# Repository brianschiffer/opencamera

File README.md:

# opencamera
an open hardware CCD camera

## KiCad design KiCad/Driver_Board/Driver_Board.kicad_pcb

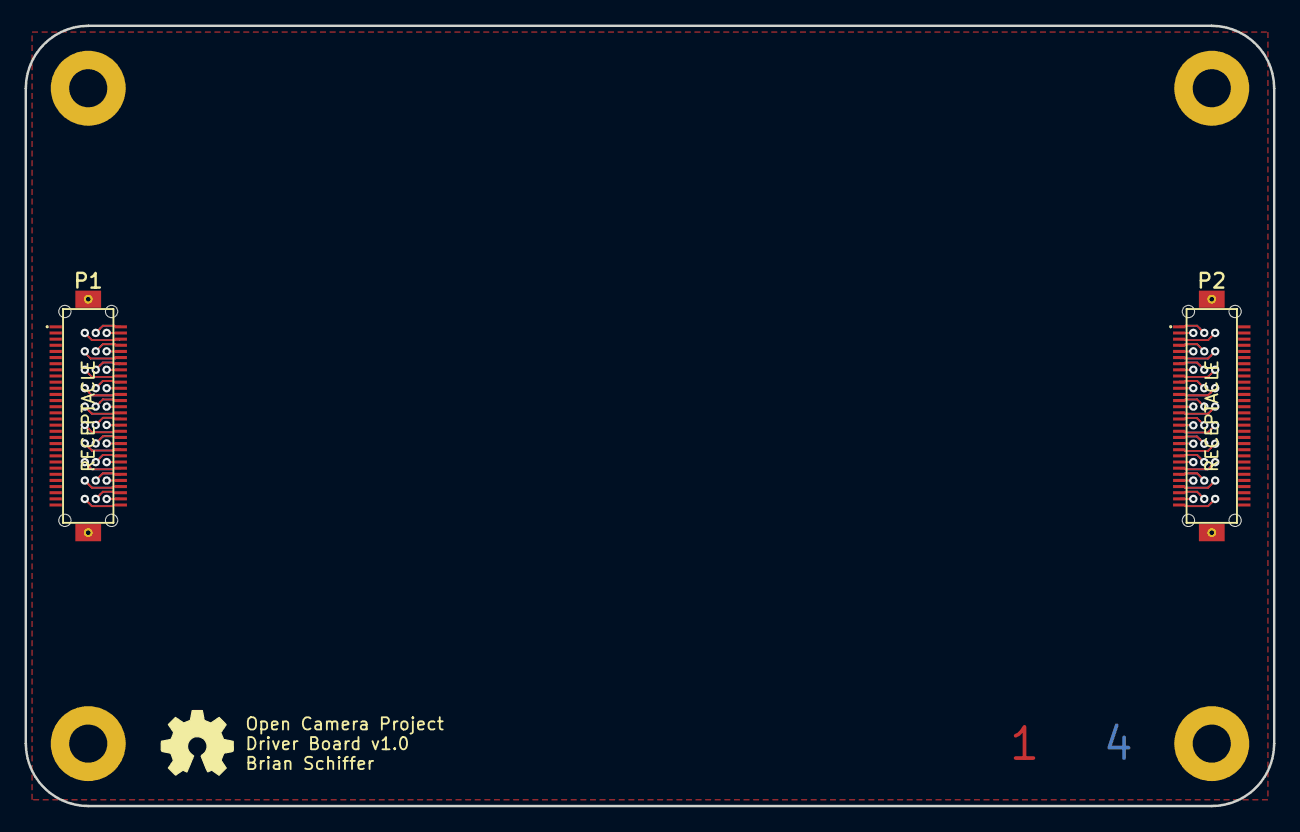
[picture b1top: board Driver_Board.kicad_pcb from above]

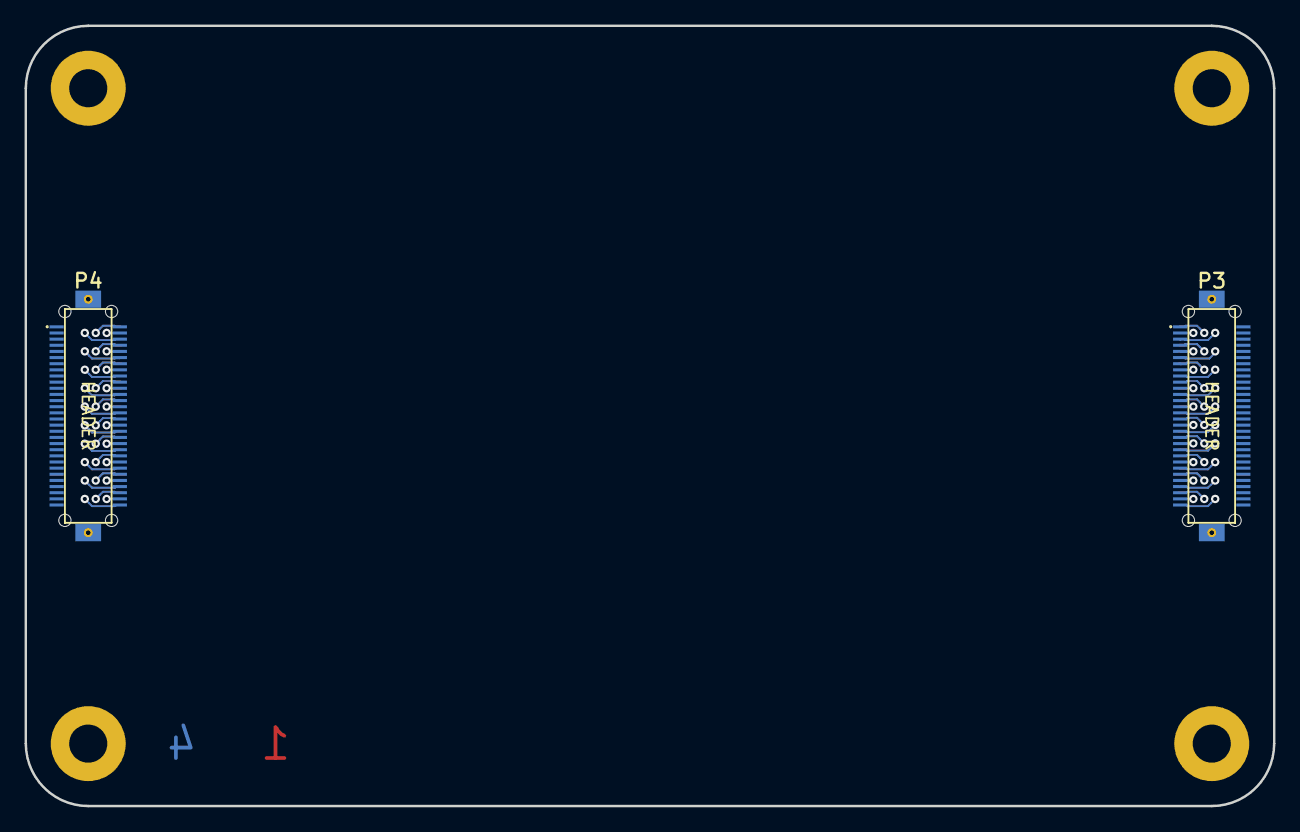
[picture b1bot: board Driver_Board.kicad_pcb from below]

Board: 4 copper layers, 101.6 x 63.5 mm, 4 parts (2 on the bottom side), 62 nets.

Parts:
P1: CONN_LEFT_TOP; DF17_60_RECEPTACLE
P2: CONN_RIGHT_TOP; DF17_60_RECEPTACLE
P3: CONN_LEFT_BOTTOM; DF17_60_HEADER
P4: CONN_RIGHT_BOTTOM; DF17_60_HEADER

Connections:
/connectors/L1: P1.2, P3.1
/connectors/L2: P1.4, P3.3
/connectors/L3: P1.6, P3.5
/connectors/L4: P1.8, P3.7
/connectors/L5: P1.10, P3.9
/connectors/L6: P1.12, P3.11
/connectors/L7: P1.14, P3.13
/connectors/L8: P1.16, P3.15
/connectors/L9: P1.18, P3.17
/connectors/L10: P1.20, P3.19
/connectors/L11: P1.22, P3.21
/connectors/L12: P1.24, P3.23
/connectors/L13: P1.26, P3.25
/connectors/L14: P1.28, P3.27
/connectors/L15: P1.30, P3.29
/connectors/L16: P1.32, P3.31
/connectors/L17: P1.34, P3.33
/connectors/L18: P1.36, P3.35
/connectors/L19: P1.38, P3.37
/connectors/L20: P1.40, P3.39
/connectors/L21: P1.42, P3.41
/connectors/L22: P1.44, P3.43
/connectors/L23: P1.46, P3.45
/connectors/L24: P1.48, P3.47
/connectors/L25: P1.50, P3.49
/connectors/L26: P1.52, P3.51
/connectors/L27: P1.54, P3.53
/connectors/L28: P1.56, P3.55
/connectors/L29: P1.58, P3.57
/connectors/L30: P1.60, P3.59
/connectors/R1: P2.1, P4.2
/connectors/R2: P2.3, P4.4
/connectors/R3: P2.5, P4.6
/connectors/R4: P2.7, P4.8
/connectors/R5: P2.9, P4.10
/connectors/R6: P2.11, P4.12
/connectors/R7: P2.13, P4.14
/connectors/R8: P2.15, P4.16
/connectors/R9: P2.17, P4.18
/connectors/R10: P2.19, P4.20
/connectors/R11: P2.21, P4.22
/connectors/R12: P2.23, P4.24
/connectors/R13: P2.25, P4.26
/connectors/R14: P2.27, P4.28
/connectors/R15: P2.29, P4.30
/connectors/R16: P2.31, P4.32
/connectors/R17: P2.33, P4.34
/connectors/R18: P2.35, P4.36
/connectors/R19: P2.37, P4.38
/connectors/R20: P2.39, P4.40
/connectors/R21: P2.41, P4.42
/connectors/R22: P2.43, P4.44
/connectors/R23: P2.45, P4.46
/connectors/R24: P2.47, P4.48
/connectors/R25: P2.49, P4.50
/connectors/R26: P2.51, P4.52
/connectors/R27: P2.53, P4.54
/connectors/R28: P2.55, P4.56
/connectors/R29: P2.57, P4.58
/connectors/R30: P2.59, P4.60
GNDA: P2.2, P2.4, P2.6, P2.8, P2.10, P2.12, P2.14, P2.16, P2.18, P2.20, P2.22, P2.24, P2.26, P2.28, P2.30, P2.32, P2.34, P2.36, P2.38, P2.40, P2.42, P2.44, P2.46, P2.48, P2.50, P2.52, P2.54, P2.56, P2.58, P2.60, P2.61, P2.62, P4.1, P4.3, P4.5, P4.7, P4.9, P4.11, P4.13, P4.15, P4.17, P4.19, P4.21, P4.23, P4.25, P4.27, P4.29, P4.31, P4.33, P4.35, P4.37, P4.39, P4.41, P4.43, P4.45, P4.47, P4.49, P4.51, P4.53, P4.55, P4.57, P4.59, P4.61, P4.62
GNDD: P1.1, P1.3, P1.5, P1.7, P1.9, P1.11, P1.13, P1.15, P1.17, P1.19, P1.21, P1.23, P1.25, P1.27, P1.29, P1.31, P1.33, P1.35, P1.37, P1.39, P1.41, P1.43, P1.45, P1.47, P1.49, P1.51, P1.53, P1.55, P1.57, P1.59, P1.61, P1.62, P3.2, P3.4, P3.6, P3.8, P3.10, P3.12, P3.14, P3.16, P3.18, P3.20, P3.22, P3.24, P3.26, P3.28, P3.30, P3.32, P3.34, P3.36, P3.38, P3.40, P3.42, P3.44, P3.46, P3.48, P3.50, P3.52, P3.54, P3.56, P3.58, P3.60, P3.61, P3.62

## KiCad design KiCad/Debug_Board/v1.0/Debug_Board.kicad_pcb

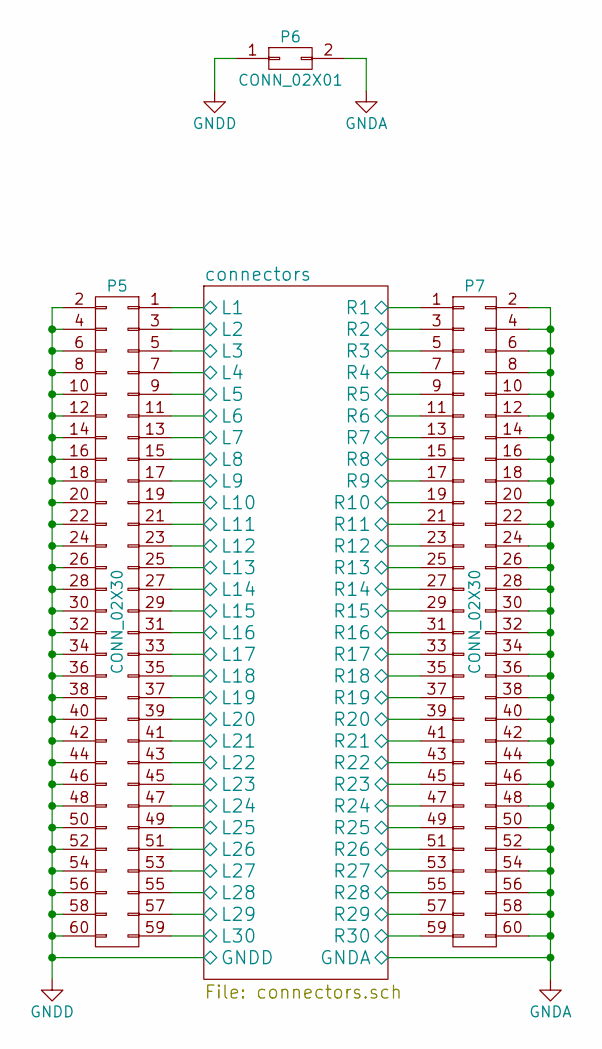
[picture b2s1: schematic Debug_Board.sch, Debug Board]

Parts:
P5, P7: CONN_02X30
P6: CONN_02X01

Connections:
/connectors/L1: P5.1; also elsewhere on the board
/connectors/L2: P5.3; also elsewhere on the board
/connectors/L3: P5.5; also elsewhere on the board
/connectors/L4: P5.7; also elsewhere on the board
/connectors/L5: P5.9; also elsewhere on the board
/connectors/L6: P5.11; also elsewhere on the board
/connectors/L7: P5.13; also elsewhere on the board
/connectors/L8: P5.15; also elsewhere on the board
/connectors/L9: P5.17; also elsewhere on the board
/connectors/L10: P5.19; also elsewhere on the board
/connectors/L11: P5.21; also elsewhere on the board
/connectors/L12: P5.23; also elsewhere on the board
/connectors/L13: P5.25; also elsewhere on the board
/connectors/L14: P5.27; also elsewhere on the board
/connectors/L15: P5.29; also elsewhere on the board
/connectors/L16: P5.31; also elsewhere on the board
/connectors/L17: P5.33; also elsewhere on the board
/connectors/L18: P5.35; also elsewhere on the board
/connectors/L19: P5.37; also elsewhere on the board
/connectors/L20: P5.39; also elsewhere on the board
/connectors/L21: P5.41; also elsewhere on the board
/connectors/L22: P5.43; also elsewhere on the board
/connectors/L23: P5.45; also elsewhere on the board
/connectors/L24: P5.47; also elsewhere on the board
/connectors/L25: P5.49; also elsewhere on the board
/connectors/L26: P5.51; also elsewhere on the board
/connectors/L27: P5.53; also elsewhere on the board
/connectors/L28: P5.55; also elsewhere on the board
/connectors/L29: P5.57; also elsewhere on the board
/connectors/L30: P5.59; also elsewhere on the board
/connectors/R1: P7.1; also elsewhere on the board
/connectors/R2: P7.3; also elsewhere on the board
/connectors/R3: P7.5; also elsewhere on the board
/connectors/R4: P7.7; also elsewhere on the board
/connectors/R5: P7.9; also elsewhere on the board
/connectors/R6: P7.11; also elsewhere on the board
/connectors/R7: P7.13; also elsewhere on the board
/connectors/R8: P7.15; also elsewhere on the board
/connectors/R9: P7.17; also elsewhere on the board
/connectors/R10: P7.19; also elsewhere on the board
/connectors/R11: P7.21; also elsewhere on the board
/connectors/R12: P7.23; also elsewhere on the board
/connectors/R13: P7.25; also elsewhere on the board
/connectors/R14: P7.27; also elsewhere on the board
/connectors/R15: P7.29; also elsewhere on the board
/connectors/R16: P7.31; also elsewhere on the board
/connectors/R17: P7.33; also elsewhere on the board
/connectors/R18: P7.35; also elsewhere on the board
/connectors/R19: P7.37; also elsewhere on the board
/connectors/R20: P7.39; also elsewhere on the board
/connectors/R21: P7.41; also elsewhere on the board
/connectors/R22: P7.43; also elsewhere on the board
/connectors/R23: P7.45; also elsewhere on the board
/connectors/R24: P7.47; also elsewhere on the board
/connectors/R25: P7.49; also elsewhere on the board
/connectors/R26: P7.51; also elsewhere on the board
/connectors/R27: P7.53; also elsewhere on the board
/connectors/R28: P7.55; also elsewhere on the board
/connectors/R29: P7.57; also elsewhere on the board
/connectors/R30: P7.59; also elsewhere on the board
GNDA: P6.2, P7.2, P7.4, P7.6, P7.8, P7.10, P7.12, P7.14, P7.16, P7.18, P7.20, P7.22, P7.24, P7.26, P7.28, P7.30, P7.32, P7.34, P7.36, P7.38, P7.40, P7.42, P7.44, P7.46, P7.48, P7.50, P7.52, P7.54, P7.56, P7.58, P7.60; also elsewhere on the board
GNDD: P5.2, P5.4, P5.6, P5.8, P5.10, P5.12, P5.14, P5.16, P5.18, P5.20, P5.22, P5.24, P5.26, P5.28, P5.30, P5.32, P5.34, P5.36, P5.38, P5.40, P5.42, P5.44, P5.46, P5.48, P5.50, P5.52, P5.54, P5.56, P5.58, P5.60, P6.1; also elsewhere on the board

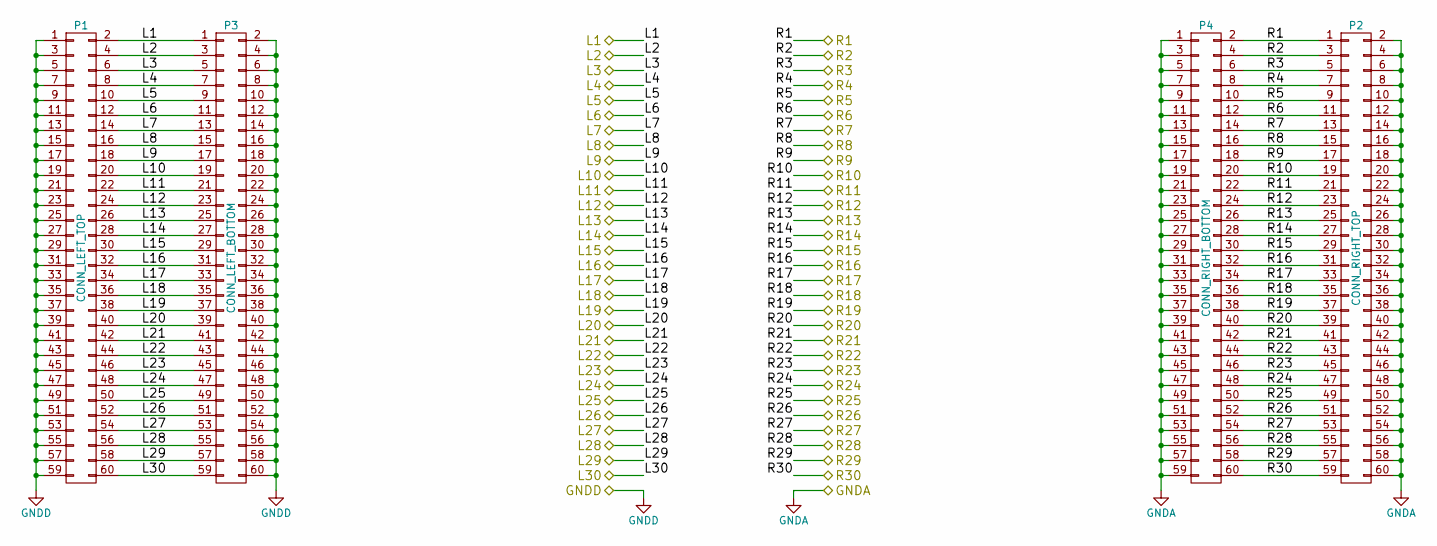
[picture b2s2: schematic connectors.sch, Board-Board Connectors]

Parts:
P1: CONN_LEFT_TOP; DF17_60_RECEPTACLE
P2: CONN_RIGHT_TOP; DF17_60_RECEPTACLE
P3: CONN_LEFT_BOTTOM; DF17_60_HEADER
P4: CONN_RIGHT_BOTTOM; DF17_60_HEADER

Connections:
/connectors/L1: P1.2, P3.1; also elsewhere on the board
/connectors/L2: P1.4, P3.3; also elsewhere on the board
/connectors/L3: P1.6, P3.5; also elsewhere on the board
/connectors/L4: P1.8, P3.7; also elsewhere on the board
/connectors/L5: P1.10, P3.9; also elsewhere on the board
/connectors/L6: P1.12, P3.11; also elsewhere on the board
/connectors/L7: P1.14, P3.13; also elsewhere on the board
/connectors/L8: P1.16, P3.15; also elsewhere on the board
/connectors/L9: P1.18, P3.17; also elsewhere on the board
/connectors/L10: P1.20, P3.19; also elsewhere on the board
/connectors/L11: P1.22, P3.21; also elsewhere on the board
/connectors/L12: P1.24, P3.23; also elsewhere on the board
/connectors/L13: P1.26, P3.25; also elsewhere on the board
/connectors/L14: P1.28, P3.27; also elsewhere on the board
/connectors/L15: P1.30, P3.29; also elsewhere on the board
/connectors/L16: P1.32, P3.31; also elsewhere on the board
/connectors/L17: P1.34, P3.33; also elsewhere on the board
/connectors/L18: P1.36, P3.35; also elsewhere on the board
/connectors/L19: P1.38, P3.37; also elsewhere on the board
/connectors/L20: P1.40, P3.39; also elsewhere on the board
/connectors/L21: P1.42, P3.41; also elsewhere on the board
/connectors/L22: P1.44, P3.43; also elsewhere on the board
/connectors/L23: P1.46, P3.45; also elsewhere on the board
/connectors/L24: P1.48, P3.47; also elsewhere on the board
/connectors/L25: P1.50, P3.49; also elsewhere on the board
/connectors/L26: P1.52, P3.51; also elsewhere on the board
/connectors/L27: P1.54, P3.53; also elsewhere on the board
/connectors/L28: P1.56, P3.55; also elsewhere on the board
/connectors/L29: P1.58, P3.57; also elsewhere on the board
/connectors/L30: P1.60, P3.59; also elsewhere on the board
/connectors/R1: P2.1, P4.2; also elsewhere on the board
/connectors/R2: P2.3, P4.4; also elsewhere on the board
/connectors/R3: P2.5, P4.6; also elsewhere on the board
/connectors/R4: P2.7, P4.8; also elsewhere on the board
/connectors/R5: P2.9, P4.10; also elsewhere on the board
/connectors/R6: P2.11, P4.12; also elsewhere on the board
/connectors/R7: P2.13, P4.14; also elsewhere on the board
/connectors/R8: P2.15, P4.16; also elsewhere on the board
/connectors/R9: P2.17, P4.18; also elsewhere on the board
/connectors/R10: P2.19, P4.20; also elsewhere on the board
/connectors/R11: P2.21, P4.22; also elsewhere on the board
/connectors/R12: P2.23, P4.24; also elsewhere on the board
/connectors/R13: P2.25, P4.26; also elsewhere on the board
/connectors/R14: P2.27, P4.28; also elsewhere on the board
/connectors/R15: P2.29, P4.30; also elsewhere on the board
/connectors/R16: P2.31, P4.32; also elsewhere on the board
/connectors/R17: P2.33, P4.34; also elsewhere on the board
/connectors/R18: P2.35, P4.36; also elsewhere on the board
/connectors/R19: P2.37, P4.38; also elsewhere on the board
/connectors/R20: P2.39, P4.40; also elsewhere on the board
/connectors/R21: P2.41, P4.42; also elsewhere on the board
/connectors/R22: P2.43, P4.44; also elsewhere on the board
/connectors/R23: P2.45, P4.46; also elsewhere on the board
/connectors/R24: P2.47, P4.48; also elsewhere on the board
/connectors/R25: P2.49, P4.50; also elsewhere on the board
/connectors/R26: P2.51, P4.52; also elsewhere on the board
/connectors/R27: P2.53, P4.54; also elsewhere on the board
/connectors/R28: P2.55, P4.56; also elsewhere on the board
/connectors/R29: P2.57, P4.58; also elsewhere on the board
/connectors/R30: P2.59, P4.60; also elsewhere on the board
GNDA: P2.2, P2.4, P2.6, P2.8, P2.10, P2.12, P2.14, P2.16, P2.18, P2.20, P2.22, P2.24, P2.26, P2.28, P2.30, P2.32, P2.34, P2.36, P2.38, P2.40, P2.42, P2.44, P2.46, P2.48, P2.50, P2.52, P2.54, P2.56, P2.58, P2.60, P4.1, P4.3, P4.5, P4.7, P4.9, P4.11, P4.13, P4.15, P4.17, P4.19, P4.21, P4.23, P4.25, P4.27, P4.29, P4.31, P4.33, P4.35, P4.37, P4.39, P4.41, P4.43, P4.45, P4.47, P4.49, P4.51, P4.53, P4.55, P4.57, P4.59; also elsewhere on the board
GNDD: P1.1, P1.3, P1.5, P1.7, P1.9, P1.11, P1.13, P1.15, P1.17, P1.19, P1.21, P1.23, P1.25, P1.27, P1.29, P1.31, P1.33, P1.35, P1.37, P1.39, P1.41, P1.43, P1.45, P1.47, P1.49, P1.51, P1.53, P1.55, P1.57, P1.59, P3.2, P3.4, P3.6, P3.8, P3.10, P3.12, P3.14, P3.16, P3.18, P3.20, P3.22, P3.24, P3.26, P3.28, P3.30, P3.32, P3.34, P3.36, P3.38, P3.40, P3.42, P3.44, P3.46, P3.48, P3.50, P3.52, P3.54, P3.56, P3.58, P3.60; also elsewhere on the board

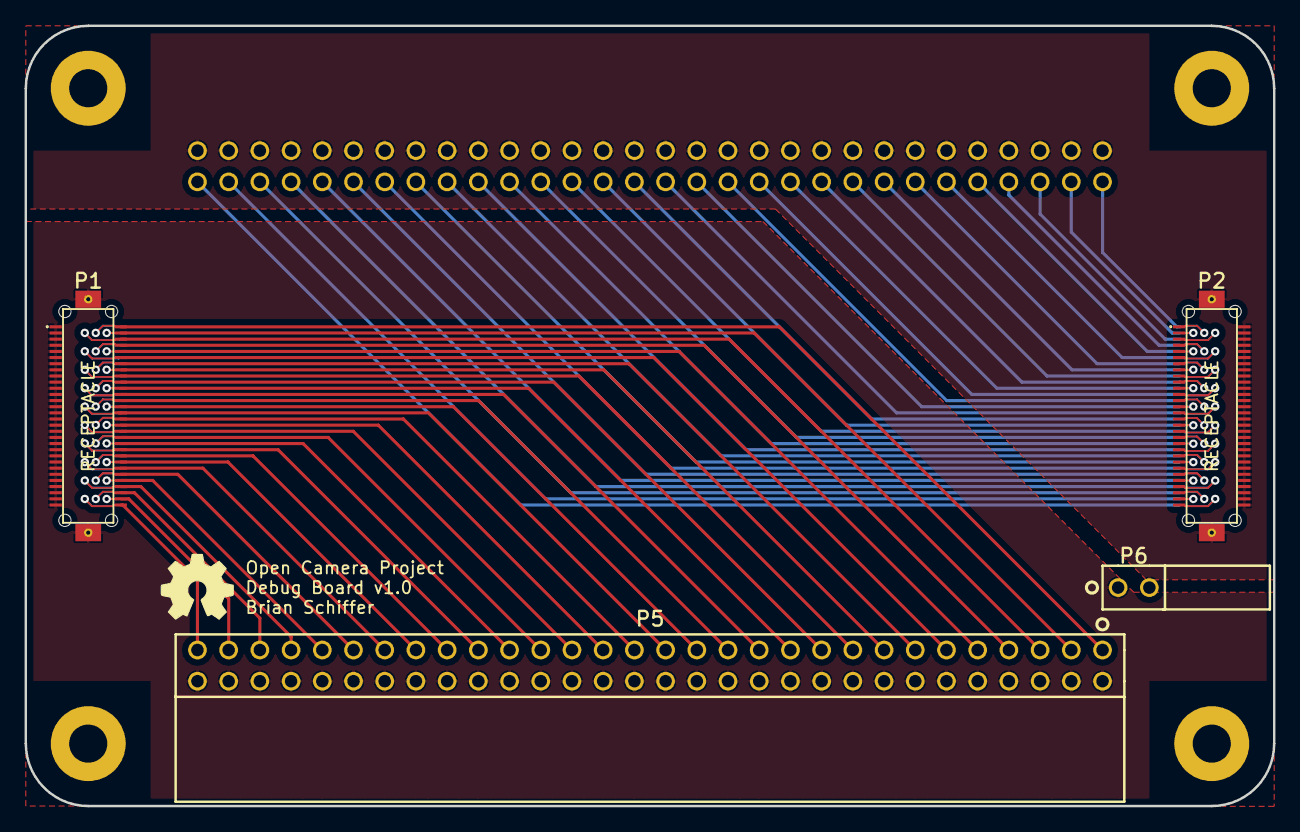
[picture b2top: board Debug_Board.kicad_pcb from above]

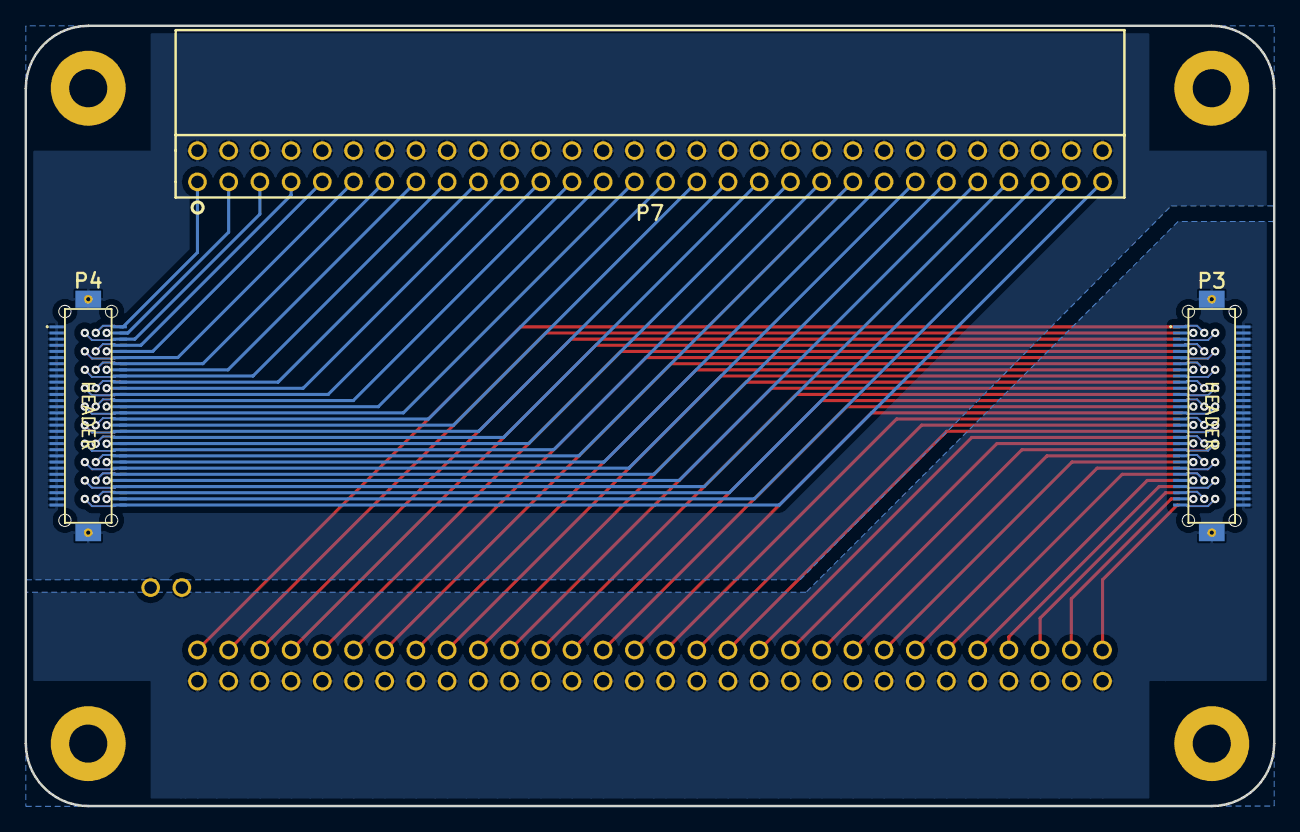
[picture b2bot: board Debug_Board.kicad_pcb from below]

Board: 4 copper layers, 101.6 x 63.5 mm, 7 parts (3 on the bottom side), 62 nets.

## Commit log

2015-06-03 Added KAI2020 CCD Datasheets & Application Notes.
    For the first version of the open camera, I am planning on using the
    KAI2020 CCD.
2015-06-07 Initial KiCad Folder & Template Draft
2015-06-07 Update template with connectors & keep-outs.
    Also fixed the naming scheme.
2015-06-07 Connected the connectors from front to back on template.
2015-06-09 Initial Debug Board Draft.
    Created & routed the debug board.
    Created a stitching via footprint for stitching ground planes.
    Edited template board to ground the board-board connectors and add
    stitching vias through the mounting pads.
2015-06-10 Cleaned up ground plane on debug board & generated gerbers.
2015-06-11 Updated board-board connectors with mounting holes.
    THIS IS THE VERSION SENT TO FAB ON JUNE 10 2015.
2015-06-13 Update Template
    v1.1
    Removed keepouts around mounting holes (looks nicer).
    Modified board-board connectors to include grounded mounting pads with
    through via.
    Created test point footprints.
    Added 1,2,3,4 layer text to confirm proper stackup when receiving from
2015-06-25 Reorginization
    A bit of cleanup + part selection for the power board.
2015-06-25 Power board started
    Created some schematic symbols for power board parts.
    Also, started the hierarchy sheets.
2015-06-28 Updated power board schematic.
    Initial schematic draft. Probably will be modified once layout is
    started.
2015-06-30 Power board fixes & Updated BOM
    Initialized refdes.
    Added test clip test points to all power lines (except DACs).
    Fixed a feedback resistor mess up on the +/-15V LDOs.
2015-06-30 Selected some BOM components.
2015-07-01 Fixed -15V LDO & Updated BOM
    -15V LDO had incorrect feedback resistors. +15V LDO seemed ok.
    BOM updated to all tentatively selected parts.
2015-07-03 Updated BOM & Schematic
    BOM was too high.
    Switched to a cheaper 8bit DAC. This will still yield ~0.06V resolution
    when gained up to +15V.
    Currently leaving power circuits alone, but in the future this could be
    better optimized for space and cost. Multichannel buck PMIC would be a
    good option to simplify the digital supplies.
2015-07-04 Created TPS63030 footprint.
    Also updated PCB sheet.
2015-07-04 Created all of the custom footprints necessary.
    Also updated the BOM to include the footprints used.
2015-07-04 Linked footprints to schematic.
    Also cleaned up some footprint errors:
    Changed IC footprint names to be invisible on the silkscreen layer.
    Fixed test points that were lacking pin numbers causing netlist
    failures.
2015-07-04 Rough PCB component placement.
    Organized parts by module and roughly placed them in appropriate
    locations on the board.
    Also fixed a couple of test points that weren't properly connected to a
    net.
2015-07-05 Added a reserved MISO pin on the board-board connectors for future SPI devices.
2015-07-05 Connected GND & GNDA since this is the power board which supplies both.
2015-07-05 Removed redundant SMD test points where test clips are being used.
2015-07-05 Some layout progress.
    Properly placed and oriented parts for compact layout of individual
    modules.
    Added zones of copper around the converters as appropriate.
2015-07-06 All nets routed! No DRC errors.
    Still needs some cleanup:
    -Check ground plane continuity.
    -Thicken power traces where possible.
    -Move SPI lines out of the way.
2015-07-06 Added a Vin test clip.
    Also did a bit of copper pour cutout cleanup.
2015-07-06 Component changes
    Switched Vref test point to test clip.
    Beefed up 0ohm jumpers to 0805.
2015-07-06 Ground plane cutout cleanup.
2015-07-07 SPI Trace Cleanup
2015-07-07 More SPI Cleanup.
2015-07-07 Thickened Power Traces.
2015-07-07 Pulled ground pour back to ensure 20mil clearance to board edge.
2015-07-07 Placed a bunch of ground plane stitching vias.
2015-07-07 Fixed missing links between ground vias for some of the thermal pads.
2015-07-07 More Cleanup
    -Moved some traces away from the inductors to help with ground plane
    continuity
    -Increased via size in power traces
    -Labeled power jumpers
2015-07-08 Added more ground vias around SPI lines.
2015-07-08 Gerbers generated and sent to Fab!
2015-07-11 Stencil Fixes
    Changed Solder Paste Clearance to 3mil.
    Changed SMD test points footprint to not have solder paste.
    Generated & ordered stencils.
2015-07-11 Stencil Fix
    Realized the solder paste clearance should be negative to bring it into
    the pads. Set to -0.001 to allow it to work even for small 0.5mm pitch
    components.
2015-07-11 Updated Template
    -Added default -0.001 paste clearance.
    -Added a reference copper pour so I won't have to remember the exact
    dimensions away from board edge.
2015-07-11 Fixed Template Ground Pour
    Now properly uses fillet corners to fully fill the board around mounting
    holes. Looks a lot nicer.
2015-07-12 Added more trace & via options to template.
2015-07-12 Created battery board schematic.
2015-07-12 Added DNP Pull-Up Resistors.
    Just in case there is a need to pull-up the lines on-board.
2015-07-12 Created & assigned footprints.
2015-07-13 Added power switch.
2015-07-14 Initial part placement.
    Also added cutouts around the battery for a battery strap.
2015-07-15 Completed routing for battery board.
    No DRC errors!
2015-07-15 Ground plane cleanup.
    -Got rid of battery pour cutout on bottom layer.
    -Made the ground pour solid around the battery connector.
2015-07-16 Fixed cutouts & generated gerbers for battery board.
    -Cutouts were on the wrong layer
    -Bottom copper pour needed cutouts around the cutouts
    -Gerbers sent to fab!
2015-07-25 Reference document reorganization
    Reorganizing datasheets and application notes now that I might be using
    the KAI-4021 sensor instead of the KAI-2020.
2015-08-03 Part Changes
    Fixes some mistakes made when choosing feedback resistors.
    R17: 1.8M -> 2.1M
    R18: 180k -> 210k
    R25: 20k -> 115k
    R20: 49.9k -> 523k
2015-08-03 Generated Battery Board Solder Paste Stencil.
2015-12-30 Initialized Driver Board Schematic & PCB from template
    (also updated power board for the kicad version on my new computer)
2015-12-30 Updated connectors to reflect power board nets
